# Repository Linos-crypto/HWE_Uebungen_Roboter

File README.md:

# HWE – Roboter

Felix Mähr und Linus Kimpfler · Hardwareentwicklung · Stand: 22. Oktober 2026

> Hardware-Zwischenstand vor der geplanten PCB-Bestellung. Schaltplan und Layout sind nach Angabe der Projektgruppe erstellt. Das Projekt ist noch nicht abgeschlossen; Fertigung, Bestückung und Funktionsprüfung sind nicht als abgeschlossen dokumentiert.

Eine eigene Steuerplatine für einen kleinen Roboter mit zwei unabhängig ansteuerbaren DC-Motoren: ATmega328P, zwei Motortreiber, BMI323 als vorgesehenem Bewegungssensor, drei Tastern und einem I²C-OLED.

[Schaltplan](#schaltplan) · [PCB](#leiterplatte) · [Pinbelegung](#pinbelegung) · [HTML-BOM](HWE_Uebungen_Roboter/bom/ibom.html) · [Offene Punkte](#offene-punkte)

## Inhaltsverzeichnis

1. [Projektstand und Grundlagen](#projektstand-und-grundlagen)
2. [Dateien und Projekt öffnen](#dateien-und-projekt-öffnen)
3. [Schaltplan](#schaltplan)
4. [Hardware und Versorgung](#hardware-und-versorgung)
5. [Pinbelegung](#pinbelegung)
6. [Leiterplatte](#leiterplatte)
7. [Stückliste und Bestückungshilfe](#stückliste-und-bestückungshilfe)
8. [Offene Punkte](#offene-punkte)
9. [Versionsverwaltung und nächste Projektphase](#versionsverwaltung-und-nächste-projektphase)
10. [Technische Unterlagen](#technische-unterlagen)

## Projektstand und Grundlagen

Diese Dokumentation beschreibt den Hardwareentwurf, nicht einen bereits funktionsgeprüften Roboter. Firmware und Programmierung folgen in einer späteren Projektphase und sind hier nicht enthalten. Fahrfunktion, Displayausgabe und Sensorkommunikation sind nicht als getestet dokumentiert.

Grundlagen sind die bereitgestellten KiCad-Dateien, die Repository-Unterlagen, die Angaben der Projektgruppe und die [Semiversus-Aufgabenstellung](https://www.semiversus.com/hwe/teil1_und_teil2/uebersicht.html). Die detaillierten Anschlussangaben wurden aus dem hochgeladenen KiCad-Zwischenstand abgeleitet. Nach Änderungen müssen Tabellen, Abbildungen und HTML-BOM erneut abgeglichen werden. Ein vollständiger ERC-/DRC-Lauf wurde bei der Erstellung dieser Dokumentation nicht ausgeführt.

## Dateien und Projekt öffnen

| Pfad | Inhalt |
| --- | --- |
| `Datasheets/` | Herstellerdatenblätter |
| `HWE_Uebungen_Roboter/HWE_Uebungen_Roboter.kicad_pro` | KiCad-Projekt und Entwurfsregeln |
| `HWE_Uebungen_Roboter/HWE_Uebungen_Roboter.kicad_sch` | Editierbarer Schaltplan |
| `HWE_Uebungen_Roboter/HWE_Uebungen_Roboter.kicad_pcb` | Editierbares PCB |
| `HWE_Uebungen_Roboter/Robo.kicad_sym` | Eigene Symbole |
| `HWE_Uebungen_Roboter/Robo.pretty/` | Eigene Footprints |
| `HWE_Uebungen_Roboter/sym-lib-table` und `fp-lib-table` | Bibliothekseinbindung |
| `HWE_Uebungen_Roboter/Images/` | SVG-Exporte |
| `HWE_Uebungen_Roboter/bom/ibom.html` | Interaktive Bestückungshilfe |

Das Projekt über die `.kicad_pro` öffnen und die Ordnerstruktur beibehalten. Die bereitgestellten Hauptdateien wurden mit KiCad 10.0 gespeichert. `${KIPRJMOD}` verweist auf das KiCad-Projektverzeichnis, nicht auf das Repository-Hauptverzeichnis. Eigene Bibliotheken müssen deshalb relativ zum Projekt auffindbar bleiben. Externe 3D-Modelle können zusätzliche lokale Pfadvariablen oder Bibliotheken benötigen; fehlende Modelle beweisen keinen elektrischen Fehler.

## Schaltplan

[Schaltplan in voller Größe öffnen](HWE_Uebungen_Roboter/Images/HWE_Uebungen_Roboter.svg)

Der Schaltplan umfasst Versorgung, Mikrocontroller, zwei Motorstufen, Sensor, Anzeige, Bedienelemente und Schnittstellen. Die Abbildung ist ein Export; Änderungen an der Quelldatei aktualisieren sie nicht automatisch.

## Hardware und Versorgung

| Baugruppe | Komponenten | Aufgabe |
| --- | --- | --- |
| Steuerung | U3, ATmega328P-A, TQFP-32 | Zentrale Verarbeitung und spätere Motoransteuerung |
| Versorgung | J2, U2 LM317, R1/R2, C1/C2 | Einspeisung und vorgesehene 3,3-V-Regelung |
| Linker Motor | IC1 TB67H450AFNG, R3, J3 | Eigene Vollbrücke |
| Rechter Motor | IC2 TB67H450AFNG, R4, J4 | Eigene Vollbrücke |
| Bewegungssensor | MT1, vorgesehen: BMI323 | Beschleunigung und Drehrate über SPI |
| Taster | SW1–SW3 | Eingänge gegen Masse |
| Anzeige | U1, I²C-OLED | Vorgesehene spätere Anzeige |
| Status | D1 und R6 | Separater LED-Ausgang |
| Anschlüsse | J1, J5, J6 | ISP, I²C und UART |
| Messpunkte | TP1–TP3 | GND, 3,3 V und Batterie |

### Versorgungskonzept

Nach Angabe der Projektgruppe ist eine 5-V-Batterieversorgung vorgesehen. Das Netz `+BATT` führt über J2 Pin 1 zur Motorversorgung VM und zum Eingang des LM317. J2 Pin 2 ist GND. Der vorgesehene Reglerausgang `+3V3` versorgt die Logik. TP3 trägt die Beschriftung `5V`, liegt aber direkt auf `+BATT`; ein separater geregelter 5-V-Ausgang wird damit nicht behauptet.

R1 liegt zwischen LM317-OUT und ADJ, R2 zwischen ADJ und GND. Laut TI gilt mit typisch 1,25 V Referenzspannung:

```text
Vout = Vref × (1 + R2/R1) + Iadj × R2
```

R1 und R2 sind noch nicht numerisch spezifiziert. Die tatsächliche Ausgangsspannung ist deshalb nicht allein durch den Netznamen nachgewiesen.

> Offener Auslegungspunkt: Bei 5 V Eingang und 3,3 V Ausgang bleiben 1,7 V Reserve. Das mitgelieferte LM317-Datenblatt nennt in den empfohlenen Betriebsbedingungen mindestens 3 V Eingang-Ausgang-Differenz. Eine zuverlässige 3,3-V-Regelung ist damit für diese Eingangsspannung nicht allein durch das Datenblatt abgesichert.

Beispiel, kein Messwert: Bei angenommenen 100 mA und tatsächlich erreichten 3,3 V beträgt die Verlustleistung näherungsweise `(5 − 3,3) V × 0,1 A = 0,17 W`, ohne Zusatzanteile. Das belegt weder Regelfähigkeit noch thermische Freigabe.

### Motorstufen

Jeder Motor erhält einen eigenen TB67H450AFNG. VM liegt an `+BATT`, VREF an `+3V3`, das Exposed Pad an GND. R3 beziehungsweise R4 verbinden RS mit GND. Da ihre Werte offen sind, wird keine konkrete Stromgrenze angegeben.

IN1 und IN2 werden durch die in der Pinbelegung genannten Timer-fähigen Mikrocontrollerpins angesteuert. Ein zusätzlicher separater PWM-Eingang ist nicht vorgesehen dokumentiert. Die konkrete Ansteuerung folgt erst mit der Firmware. Motor-Nennstrom, Anlauf-/Blockierstrom, Widerstandsbelastbarkeit und Wärmeabfuhr sind noch zu bewerten.

### Sensor, Bedienelemente und Anzeige

Bestückt werden soll der BMI323. Im 4-Draht-SPI-Betrieb nennt Bosch Pin 1 SDO, Pin 12 CSB, Pin 13 SCx und Pin 14 SDx. Pin 5 ist VDDIO, Pin 8 VDD, Pin 6 GNDIO und Pin 7 GND. Vorgesehen sind 3,3 V Versorgung. Pinbelegung, Padgeometrie und Orientierung müssen vor der Bestellung vollständig mit dem Originaldatenblatt abgeglichen werden; eine geprüfte Austauschbarkeit wird hier nicht behauptet.

R5 ist als 100-kΩ-Pull-up für CS und R7 als 100-kΩ-Pull-up für RESET eingetragen. Der CS-Pull-up soll den Sensor bei nicht aktivem Mikrocontroller abwählen. SPI-Leitungen werden auch für ISP genutzt; der inaktive Sensorzustand ist deshalb bei der späteren Programmierung relevant.

SW1–SW3 schalten gegen Masse. Die Aufgabenstellung sieht interne Mikrocontroller-Pull-ups für definierte unbetätigte Pegel vor. Aktivierung und Entprellung sind noch keine implementierten Funktionen dieses Zwischenstands.

Das OLED nutzt SDA/SCL gemeinsam mit J5. Vor Inbetriebnahme sind Modul-Pinfolge, Versorgung und vorhandene I²C-Pull-ups zu prüfen. Displayinhalte oder erfolgreiche Kommunikation sind nicht nachgewiesen.

## Pinbelegung

### ATmega328P im TQFP-32

| Funktion | Port / Zusatzfunktion | Gehäusepin | Netz / Ziel |
| --- | --- | --- | --- |
| Linker Motor IN2 | PB1 / OC1A | 13 | Richtung 1 links → IC1 Pin 2 |
| Linker Motor IN1 | PB2 / OC1B | 14 | Richtung 2 links → IC1 Pin 3 |
| Rechter Motor IN2 | PD5 / OC0B | 9 | Richtung 1 rechts → IC2 Pin 2 |
| Rechter Motor IN1 | PD6 / OC0A | 10 | Richtung 2 rechts → IC2 Pin 3 |
| SPI MOSI | PB3 | 15 | MOSI, Sensor und ISP |
| SPI MISO | PB4 | 16 | MISO, Sensor und ISP |
| SPI SCK | PB5 | 17 | SCK, Sensor und ISP |
| Sensor Chip Select | PC3 | 26 | CS |
| I²C SDA | PC4 | 27 | SDA |
| I²C SCL | PC5 | 28 | SCL |
| Reset | PC6 / RESET | 29 | RST |
| UART RXD | PD0 | 30 | RXD |
| UART TXD | PD1 | 31 | TXD |
| Linker Taster | PC0 | 23 | swl |
| Mittlerer Taster | PC1 | 24 | swm |
| Rechter Taster | PC2 | 25 | swr |
| LED | PB0 | 12 | LED → R6 → D1 → GND |

XTAL1 und XTAL2 sind im bereitgestellten Entwurf unbeschaltet; ein externer Quarz ist nicht vorgesehen bestückt. Die spätere Taktfrequenz hängt von Taktquelle und Fuse-Einstellungen ab. Sie ist hier nicht als programmiert dokumentiert.

### Steckverbinder und Testpunkte

| Anschluss | Belegung nach elektrischer Pinnummer |
| --- | --- |
| J1, AVR-ISP-6 | 1 MISO; 2 +3V3; 3 SCK; 4 MOSI; 5 RST; 6 GND |
| J2, Batterie | 1 +BATT; 2 GND |
| J3, linker Motor | 1 IC1 OUT1; 2 IC1 OUT2 |
| J4, rechter Motor | 1 IC2 OUT1; 2 IC2 OUT2 |
| J5, I²C | 1 GND; 2 +3V3; 3 SCL; 4 SDA |
| J6, UART | 1 GND; 2 TXD; 3 RXD; 4 +3V3 |
| TP1 | GND |
| TP2 | +3V3 |
| TP3 | +BATT, beschriftet mit 5V |

Die Tabelle ist keine räumliche Steckeransicht. Pin-1-Markierungen und Gegenstecker vor dem Anschluss prüfen. UART ist eine Mikrocontroller-Signalschnittstelle; eine RS-232-Pegelwandlung ist nicht dokumentiert.

## Leiterplatte

[PCB-Plot öffnen](HWE_Uebungen_Roboter/Images/HWE_Uebungen_Roboter-Edge_Cuts.svg) · [Vorderes Kupfer](HWE_Uebungen_Roboter/Images/HWE_Uebungen_Roboter-F_Cu.svg) · [Bestückungsdruck](HWE_Uebungen_Roboter/Images/HWE_Uebungen_Roboter-F_Silkscreen.svg)

Im PCB sind zwei Kupferlagen (`F.Cu`, `B.Cu`), 1,6 mm Gesamtdicke, FR4 und 35 µm Kupfer pro Lage eingetragen. Das sind Entwurfsangaben, keine bestätigten Bestellparameter. Die Kontur kombiniert einen rechteckigen Bereich mit einer halbrunden Vorderseite. Die Ausdehnung des bereitgestellten Entwurfs beträgt 93 × 64 mm; sechs Bohrungen H1–H6 verwenden 3,2-mm-M3-Footprints.

### Entwurfsregeln

| Netzklasse | Vorgabe Leiterbahnbreite | Clearance | Via / Bohrung |
| --- | --- | --- | --- |
| Default | 0,25 mm | 0,15 mm | 0,60 / 0,30 mm |
| +3V3 | 0,40 mm | 0,15 mm | 0,60 / 0,30 mm |
| +BATT | 1,00 mm | 0,15 mm | 0,60 / 0,30 mm |

`+3V3` und `+BATT` werden über gleichnamige Netzmuster zugeordnet. Globale Mindestwerte: 0,15 mm Kupferabstand, 0,25 mm Leiterbahnbreite und 0,25 mm Kupfer-Randabstand. Netzklassen sind Vorgaben, kein Nachweis identischer Breiten aller vorhandenen Segmente.

Im ausgewerteten Zwischenstand sind die `+BATT`-Leiterbahnen 1,00 mm breit, die vier Motorausgangsnetze 0,25 mm. Nach berichteter Rücksprache mit der Lehrperson wurden die Motorausgangsbreiten wegen des als gering eingeschätzten Motorstroms beibehalten. Reale Betriebs-/Blockierstromwerte und ein rechnerischer Stromtragfähigkeitsnachweis liegen nicht vor. Die Aufgabenstellung nennt ungefähr 1 A für Motorstrompfade und eine Faustregel von 1 mm/A. Die Abweichung ist dokumentiert, nicht rechnerisch freigegeben.

Die geforderten 6 mm freier PCB-Rand für die Rahmenauflage sind eine mechanische Anforderung, nicht der Kupfer-Randabstand. Ein vollständiger Nachweis ihrer Einhaltung liegt dieser Dokumentation nicht bei. Ein gespeichertes Layout oder ein Bild ersetzt keinen ERC-/DRC-Bericht.

## Stückliste und Bestückungshilfe

[Interaktive HTML-BOM öffnen](HWE_Uebungen_Roboter/bom/ibom.html)

Die mit InteractiveHtmlBom erzeugte Datei zur Nutzung herunterladen oder das Repository klonen und `ibom.html` lokal im Browser öffnen. Der GitHub-Link führt zunächst zur Dateiansicht; eine separate Webseite wurde nicht eingerichtet.

Die BOM ordnet Referenzbezeichnungen den Bestückungspositionen zu. Sie übernimmt PCB-Daten und muss nach Änderungen neu exportiert werden. Sie ist noch keine vollständig spezifizierte Einkaufs- oder Bestellliste.

| Referenzen | Eingetragener Wert / Status |
| --- | --- |
| C3–C7 | Jeweils 100 nF |
| R5, R7 | Jeweils 100 kΩ |
| R1, R2 | R; Reglerbeschaltung noch zu spezifizieren |
| R3, R4 | R; RS-Widerstände noch zu spezifizieren |
| R6 | R; LED-Vorwiderstand noch zu spezifizieren |
| C1, C2 | C; Kapazitäten noch zu spezifizieren |

Bestellnummern, Toleranzen, Spannungsfestigkeit und Belastbarkeit gegebenenfalls ergänzen. Der vorgesehene BMI323 muss in den Bestückungsunterlagen eindeutig identifizierbar sein.

## Offene Punkte

- [ ] R1–R4, R6, C1 und C2 festlegen und Schaltplan, PCB sowie BOM abgleichen.
- [ ] Reglerwahl bzw. 5-V-zu-3,3-V-Versorgung unter Last und Versorgungstoleranzen klären.
- [ ] BMI323-Pinbelegung, Orientierung, Padgeometrie und Abblockung vollständig prüfen.
- [ ] Motorströme einschließlich Anlauf/Blockieren ermitteln; Leiterbahnen, Vias und RS-Widerstände bewerten.
- [ ] 6-mm-Randauflage, Bohrungen, Rahmenpassung und Steckerzugänglichkeit prüfen.
- [ ] ERC und DRC mit Berichten ausführen; ignorierte Prüfkategorien gesondert bewerten.
- [ ] Herstellergrenzen sowie finale Gerber-/Bohrdaten prüfen.
- [ ] Nach Änderungen Bilder und HTML-BOM neu exportieren.

Leere Kästchen kennzeichnen fehlende dokumentierte Abschlussnachweise, nicht die Behauptung, die Projektgruppe habe keinerlei Prüfung durchgeführt. Diese README ist keine elektrische oder fertigungstechnische Freigabe.

## Versionsverwaltung und nächste Projektphase

Die `.gitignore` schließt Abgabeordner, lokale Einstellungen, Sicherungen, Sperren und temporäre Dateien aus. Projektdateien, Bibliotheken, Datenblätter, Bilder und HTML-BOM bleiben versioniert. Abgabe-ZIP-Dateien für die Lehrperson gehören nicht in den Repository-Inhalt.

Nach Hardwarefreigabe werden Bestellung, Aufbau und Messprotokolle als tatsächlich durchgeführte Schritte ergänzt. Firmware und Programmierung werden erst in der späteren Projektphase dokumentiert. Der Entwicklungsstand bleibt von nachgewiesenen Testergebnissen getrennt.

## Technische Unterlagen

- [Semiversus: Aufgabenstellung und Checkliste](https://www.semiversus.com/hwe/teil1_und_teil2/uebersicht.html)
- [ATmega328P-Datenblatt](Datasheets/Atmel-7810-Automotive-Microcontrollers-ATmega328P_Datasheet.pdf)
- [BMI323: Pinbelegung und Anschlussdiagramme](Datasheets/bst_bmi323_ds000.pdf)
- [TB67H450AFNG-Datenblatt](Datasheets/TB67H450AFNG_datasheet_en_20250730.pdf)
- [LM317: Betriebsbedingungen und Reglergleichung](Datasheets/lm317.pdf)
- [Omron-B3F-Datenblatt](Datasheets/en_b3f.pdf)

Bei Widersprüchen zwischen Beschreibung, Export und Datenblatt ist der konkrete Entwurf zu prüfen, statt eine nicht belegte Funktion anzunehmen.

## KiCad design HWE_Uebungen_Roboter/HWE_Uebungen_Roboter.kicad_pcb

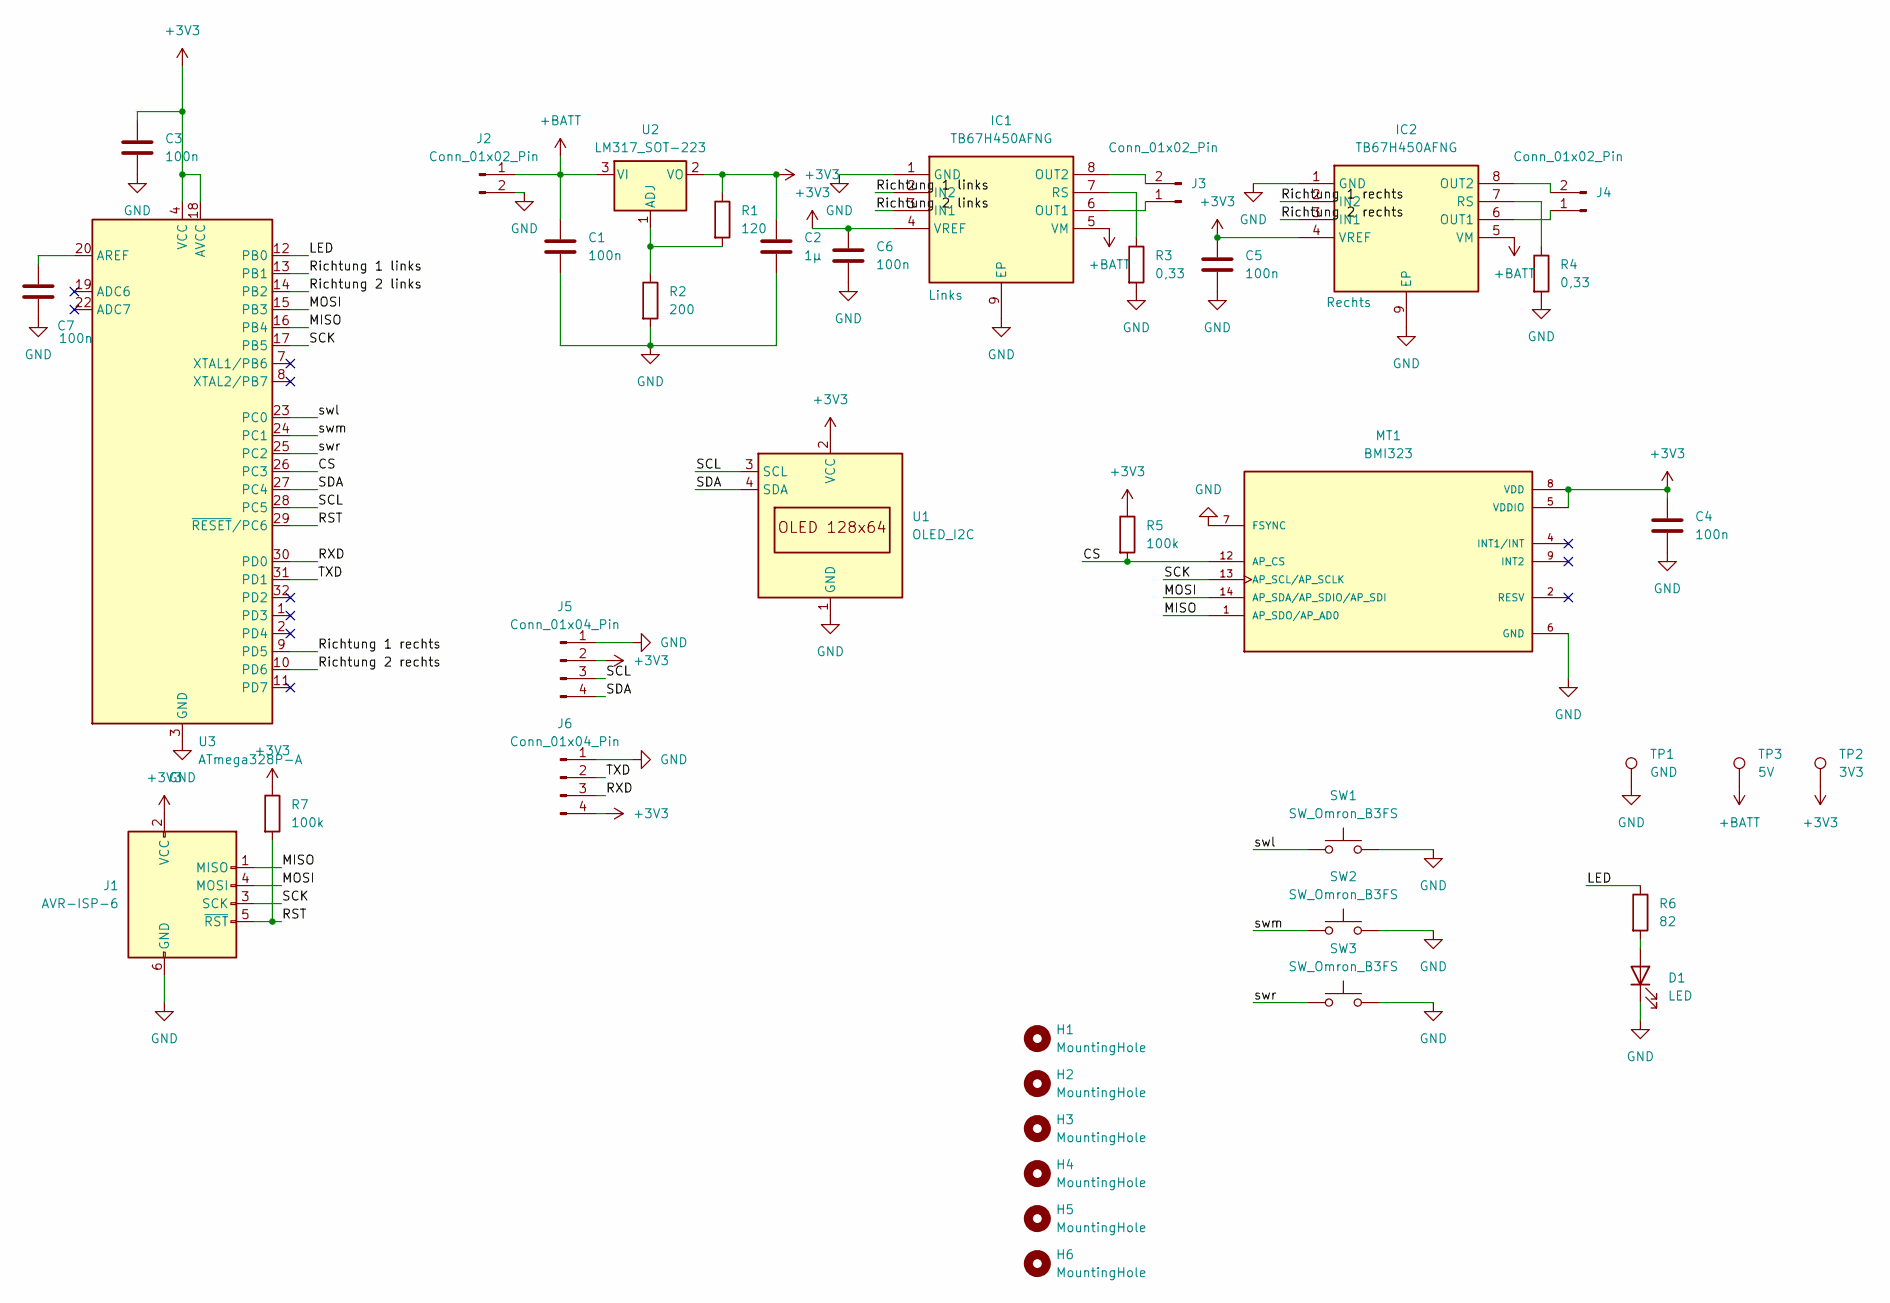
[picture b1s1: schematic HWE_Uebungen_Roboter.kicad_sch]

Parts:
C1, C3, C4, C5, C6, C7: 100n; C_0805_2012Metric_Pad1.18x1.45mm_HandSolder
C2: 1µ; C_0805_2012Metric_Pad1.18x1.45mm_HandSolder
D1: LED; LED_0805_2012Metric_Pad1.15x1.40mm_HandSolder
H1, H2, H3, H4, H5, H6: MountingHole; MountingHole_3.2mm_M3
IC1, IC2: TB67H450AFNG; P-HSOP8-0405-1.27-002; Manufacturer_Part_Number TB67H450AFNG; Mouser Part Number N/A
J1: AVR-ISP-6; IDC-Header_2x03_P2.54mm_Vertical
J2: Conn_01x02_Pin; PinHeader_1x02_P2.54mm_Vertical
J3, J4: Conn_01x02_Pin; SolderWire-0.5sqmm_1x02_P4.6mm_D0.9mm_OD2.1mm
J5, J6: Conn_01x04_Pin; PinHeader_1x04_P2.54mm_Vertical
MT1: BMI323; XDCR_ICM-42670-P; PARTREV 1.1
R1: 120; R_0805_2012Metric_Pad1.20x1.40mm_HandSolder
R2: 200; R_0805_2012Metric_Pad1.20x1.40mm_HandSolder
R3, R4: 0,33; R_0805_2012Metric_Pad1.20x1.40mm_HandSolder
R5, R7: 100k; R_0805_2012Metric_Pad1.20x1.40mm_HandSolder
R6: 82; R_0805_2012Metric_Pad1.20x1.40mm_HandSolder
SW1, SW2, SW3: SW_Omron_B3FS; SW_SPST_Omron_B3F-315x_Angled
TP1: GND; TestPoint_Bridge_Pitch5.08mm_Drill0.7mm
TP2: 3V3; TestPoint_Pad_2.0x2.0mm
TP3: 5V; TestPoint_Pad_2.0x2.0mm
U1: OLED_I2C; OLED_SSD1306_I2C_0.96
U2: LM317_SOT-223; SOT-223-3_TabPin2
U3: ATmega328P-A; TQFP-32_7x7mm_P0.8mm

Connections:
+3V3: C2.1, C3.1, C4.1, C5.1, C6.1, IC1.4 (VREF), IC2.4 (VREF), J1.2 (VCC), J5.2, J6.4, MT1.5 (VDDIO), MT1.8 (VDD), R1.1, R5.1, R7.1, TP2.1 (1_1), U1.2 (VCC), U2.2 (VO), U3.4 (VCC), U3.6 (VCC), U3.18 (AVCC)
+BATT: C1.1, IC1.5 (VM), IC2.5 (VM), J2.1, TP3.1 (1_1), U2.3 (VI)
/CS: MT1.12 (AP_CS), R5.2, U3.26 (PC3)
/LED: R6.1, U3.12 (PB0)
/MISO: J1.1 (MISO), MT1.1 (AP_SDO/AP_AD0), U3.16 (PB4)
/MOSI: J1.4 (MOSI), MT1.14 (AP_SDA/AP_SDIO/AP_SDI), U3.15 (PB3)
/RST: J1.5 (~RST), R7.2, U3.29 (~RESET/PC6)
/RXD: J6.3, U3.30 (PD0)
/Richtung 1 links: IC1.2 (IN2), U3.13 (PB1)
/Richtung 1 rechts: IC2.2 (IN2), U3.9 (PD5)
/Richtung 2 links: IC1.3 (IN1), U3.14 (PB2)
/Richtung 2 rechts: IC2.3 (IN1), U3.10 (PD6)
/SCK: J1.3 (SCK), MT1.13 (AP_SCL/AP_SCLK), U3.17 (PB5)
/SCL: J5.3, U1.3 (SCL), U3.28 (PC5)
/SDA: J5.4, U1.4 (SDA), U3.27 (PC4)
/TXD: J6.2, U3.31 (PD1)
/swl: SW1.1, U3.23 (PC0)
/swm: SW2.1, U3.24 (PC1)
/swr: SW3.1, U3.25 (PC2)
GND: C1.2, C2.2, C3.2, C4.2, C5.2, C6.2, C7.2, D1.1 (K), IC1.1 (GND), IC1.9 (EP), IC2.1 (GND), IC2.9 (EP), J1.6 (GND), J2.2, J5.1, J6.1, MT1.6 (GND), MT1.7 (FSYNC), R2.2, R3.2, R4.2, SW1.2, SW2.2, SW3.2, TP1.1 (1_1), U1.1 (GND), U3.3 (GND), U3.5 (GND), U3.21 (GND)
unnamed: D1.2 (A), R6.2
unnamed: IC1.6 (OUT1), J3.1
unnamed: IC1.8 (OUT2), J3.2
unnamed: IC1.7 (RS), R3.1
unnamed: IC2.6 (OUT1), J4.1
unnamed: IC2.8 (OUT2), J4.2
unnamed: IC2.7 (RS), R4.1
unnamed: R1.2, R2.1, U2.1 (ADJ)
unnamed: C7.1, U3.20 (AREF)

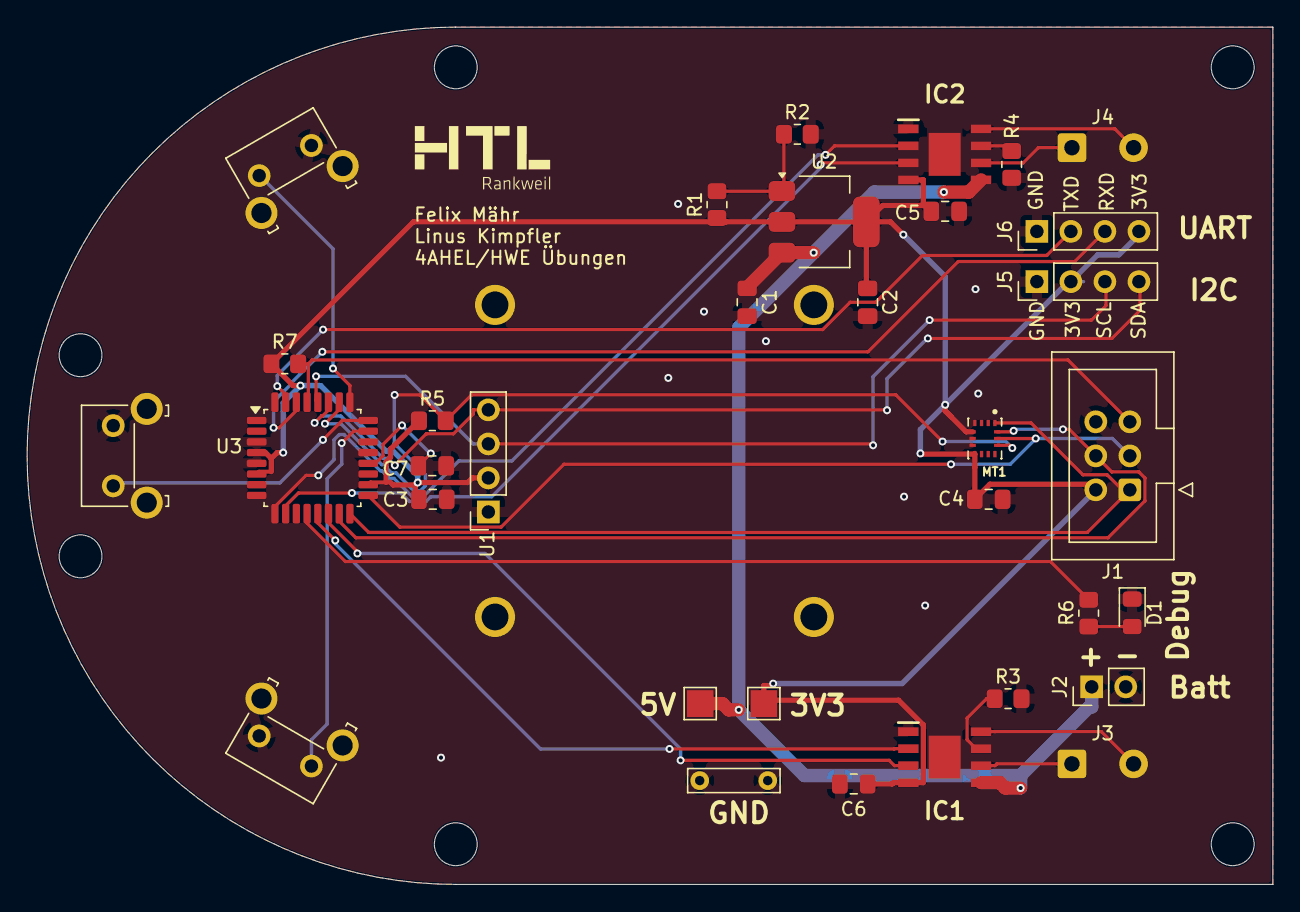
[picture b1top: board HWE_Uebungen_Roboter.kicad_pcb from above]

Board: 2 copper layers, 93.0 x 64.0 mm, 39 parts (0 on the bottom side), 29 nets.
